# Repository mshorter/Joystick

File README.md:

# Joystick

ATMega32U4  based joystick with XBee slot

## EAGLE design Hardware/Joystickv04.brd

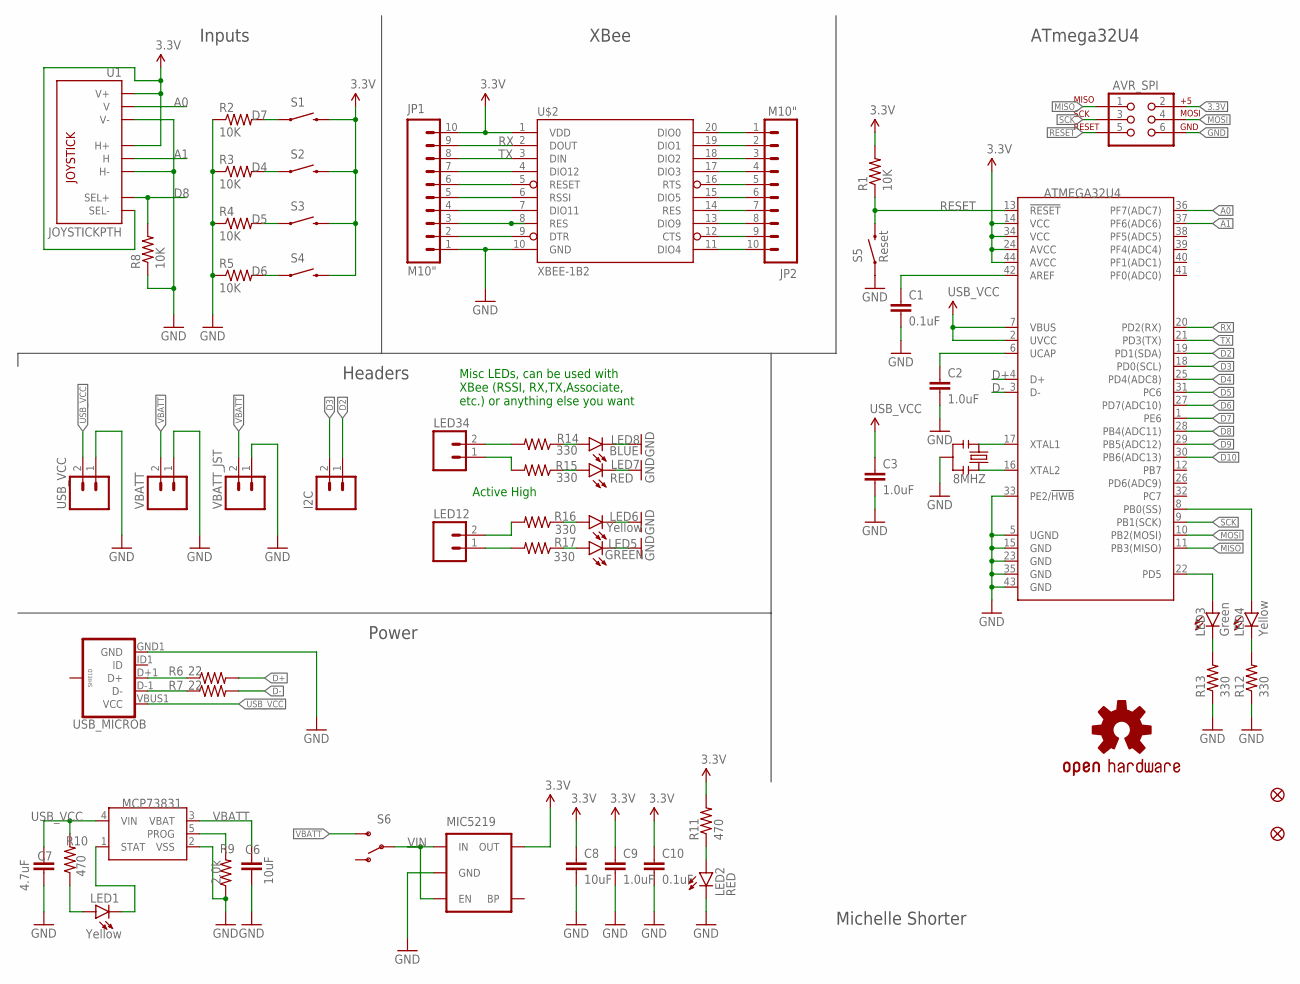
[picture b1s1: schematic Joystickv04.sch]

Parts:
ATMEGA32U4: ATMEGA32U41:1-LESS_PASTE; QFN-44-NOPAD_1:1-LESS_PASTE
AVR_SPI: AVR_SPI_PRG_6PTH; 2X3
C1, C10: 0.1uF; 0603-CAP
C2, C3, C9: 1.0uF; 0603-CAP
C6, C8: 10uF; 0603-CAP
C7: 4.7uF; 0603-CAP
FID1, FID2: FIDUCIALUFIDUCIAL; MICRO-FIDUCIAL
I2C: M02PTH; 1X02
JP1, JP2: M10"; 1X10
LED1, LED4, LED6: Yellow; LED-0603
LED2, LED7: RED; LED-0603
LED3: Green; LED-0603
LED5: GREEN; LED-0603
LED8: BLUE; LED-0603
LED12, LED34: M02PTH; 1X02
LOGO1: OSHW-LOGOM; OSHW-LOGO-M
MIC5219: V_REG_MIC5219SMD; SOT23-5
R1, R2, R3, R4, R5, R8: 10K; 0603-RES
R6, R7: 22; 0603-RES
R9: 2.0k; 0603-RES
R10, R11: 470; 0603-RES
R12, R13, R14, R15, R16, R17: 330; 0603-RES
S1, S2, S3, S4: SWITCH-MOMENTARY-212MM; TACTILE-PTH-12MM
S5: Reset; TACTILE-SWITCH-SMD
S6: SWITCH-SPDTPTH; SWITCH-SPDT
U1: JOYSTICKPTH; JOYSTICK
U4: MCP73831; SOT23-5
U$2: XBEE-1B2; XBEE-SILK
U$3: 8MHZ; RESONATOR-SMD
USB_MICROB: USB_MICROB_PLUGCONN-11752; USB-B-MICRO-SMD_V03
USB_VCC: M02PTH; 1X02
VBATT: M02PTH; 1X02
VBATT_JST: M02-JST-2MM-SMT; JST-2-SMD

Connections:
3.3V: ATMEGA32U4.14 (VCC), ATMEGA32U4.24 (AVCC), ATMEGA32U4.34 (VCC), ATMEGA32U4.44 (AVCC), AVR_SPI.2, C8.1, C9.1, C10.1, JP1.10, MIC5219.5 (OUT), R1.2, R11.2, S1.3 (2), S2.3 (2), S3.3 (2), S4.3 (2), U1.B2A (SEL-), U1.H1 (H+), U1.V1 (V+), U$2.1 (VDD)
A0: ATMEGA32U4.36 (PF7(ADC7)), U1.V2 (V)
A1: ATMEGA32U4.37 (PF6(ADC6)), U1.H2 (H)
D2: ATMEGA32U4.19 (PD1(SDA)), I2C.1
D3: ATMEGA32U4.18 (PD0(SCL)), I2C.2
D4: ATMEGA32U4.25 (PD4(ADC8)), R3.2, S2.1
D5: ATMEGA32U4.31 (PC6), R4.2, S3.1
D6: ATMEGA32U4.27 (PD7(ADC10)), R5.2, S4.1
D7: ATMEGA32U4.1 (PE6), R2.2, S1.1
D8: ATMEGA32U4.28 (PB4(ADC11)), R8.2, U1.B1A (SEL+)
D9: ATMEGA32U4.29 (PB5(ADC12))
D10: ATMEGA32U4.30 (PB6(ADC13))
D+: ATMEGA32U4.4 (D+), R6.2
D-: ATMEGA32U4.3 (D-), R7.2
GND: ATMEGA32U4.5 (UGND), ATMEGA32U4.15 (GND), ATMEGA32U4.23 (GND), ATMEGA32U4.33 (PE2/!HWB), ATMEGA32U4.35 (GND), ATMEGA32U4.43 (GND), AVR_SPI.6, C1.2, C2.2, C3.2, C6.2, C7.2, C8.2, C9.2, C10.2, JP1.1, LED2.C, LED5.C, LED6.C, LED7.C, LED8.C, MIC5219.2 (GND), R2.1, R3.1, R4.1, R5.1, R8.1, R9.1, R12.1, R13.1, S5.1, U1.H3 (H-), U1.V3 (V-), U4.2 (VSS), U$2.10 (GND), U$3.2, USB_MICROB.GND1 (GND), USB_VCC.1, VBATT.1, VBATT_JST.1
MISO: ATMEGA32U4.11 (PB3(MISO)), AVR_SPI.1
MOSI: ATMEGA32U4.10 (PB2(MOSI)), AVR_SPI.4
unnamed: ATMEGA32U4.17 (XTAL1), U$3.1
unnamed: ATMEGA32U4.42 (AREF), C1.1
unnamed: R6.1, USB_MICROB.D+1 (D+)
unnamed: JP1.2, U$2.9 (DTR)
unnamed: ATMEGA32U4.6 (UCAP), C2.1
unnamed: ATMEGA32U4.16 (XTAL2), U$3.3
unnamed: JP1.3, U$2.8 (RES)
unnamed: R7.1, USB_MICROB.D-1 (D-)
unnamed: JP1.4, U$2.7 (DIO11)
unnamed: R9.2, U4.5 (PROG)
unnamed: JP1.5, U$2.6 (RSSI)
unnamed: JP1.6, U$2.5 (RESET)
unnamed: JP1.7, U$2.4 (DIO12)
unnamed: JP2.10, U$2.11 (DIO4)
unnamed: JP2.9, U$2.12 (CTS)
unnamed: JP2.8, U$2.13 (DIO9)
unnamed: JP2.7, U$2.14 (RES)
unnamed: JP2.6, U$2.15 (DIO5)
unnamed: JP2.5, U$2.16 (RTS)
unnamed: JP2.4, U$2.17 (DIO3)
unnamed: JP2.3, U$2.18 (DIO2)
unnamed: JP2.2, U$2.19 (DIO1)
unnamed: JP2.1, U$2.20 (DIO0)
unnamed: LED2.A, R11.1
unnamed: LED1.A, R10.1
unnamed: LED1.C, U4.1 (STAT)
unnamed: ATMEGA32U4.8 (PB0(SS)), LED4.A
unnamed: LED4.C, R12.2
unnamed: LED3.C, R13.2
unnamed: ATMEGA32U4.22 (PD5), LED3.A
unnamed: LED12.1, R17.2
unnamed: LED8.A, R14.1
unnamed: LED7.A, R15.1
unnamed: LED6.A, R16.1
unnamed: LED5.A, R17.1
unnamed: LED12.2, R16.2
unnamed: LED34.1, R15.2
unnamed: LED34.2, R14.2
RESET: ATMEGA32U4.13 (!RESET), AVR_SPI.5, R1.1, S5.3 (2)
RX: ATMEGA32U4.20 (PD2(RX)), JP1.9, U$2.2 (DOUT)
SCK: ATMEGA32U4.9 (PB1(SCK)), AVR_SPI.3
TX: ATMEGA32U4.21 (PD3(TX)), JP1.8, U$2.3 (DIN)
USB_VCC: ATMEGA32U4.2 (UVCC), ATMEGA32U4.7 (VBUS), C3.1, C7.1, R10.2, U4.4 (VIN), USB_MICROB.VBUS1 (VCC), USB_VCC.2
VBATT: C6.1, S6.3 (S), U4.3 (VBAT), VBATT.2, VBATT_JST.2
VIN: MIC5219.1 (IN), MIC5219.3 (EN), S6.2

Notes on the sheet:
Misc LEDs, can be used with XBee (RSSI, RX,TX,Associate, etc.) or anything else you want
Active High
Michelle Shorter
Inputs
XBee
ATmega32U4
Headers
Power

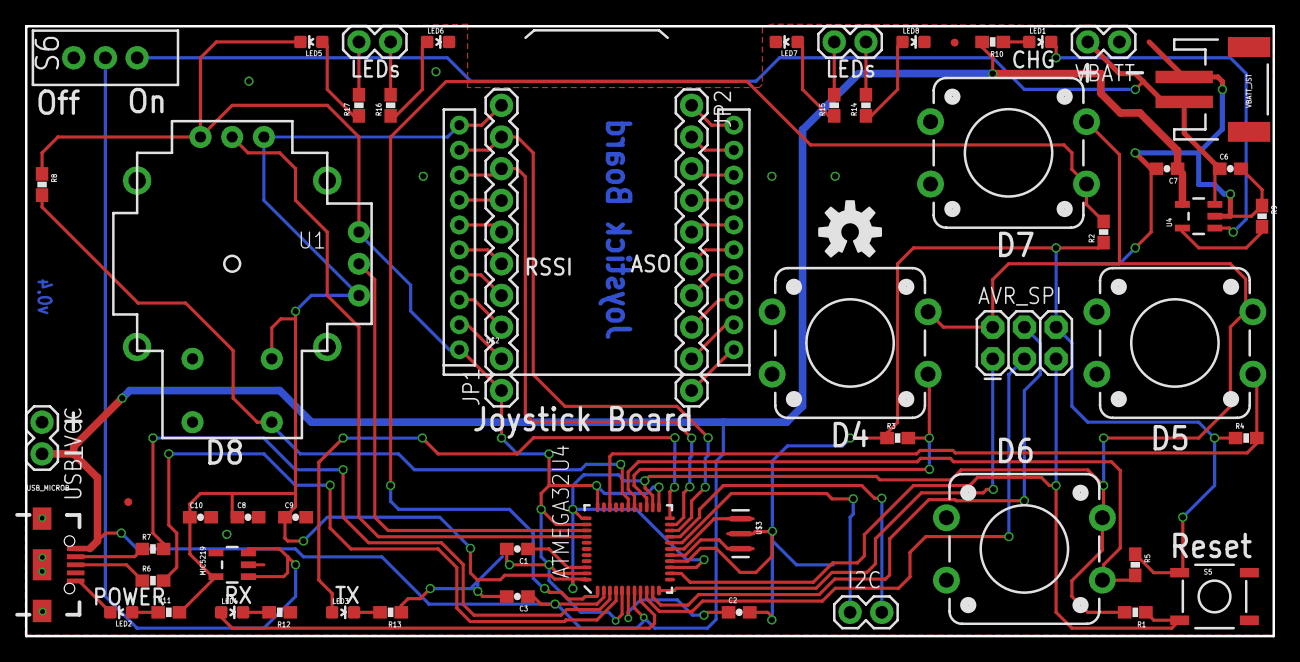
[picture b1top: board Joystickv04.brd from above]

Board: 2 copper layers, 100.0 x 48.9 mm, 58 parts (0 on the bottom side), 60 nets.

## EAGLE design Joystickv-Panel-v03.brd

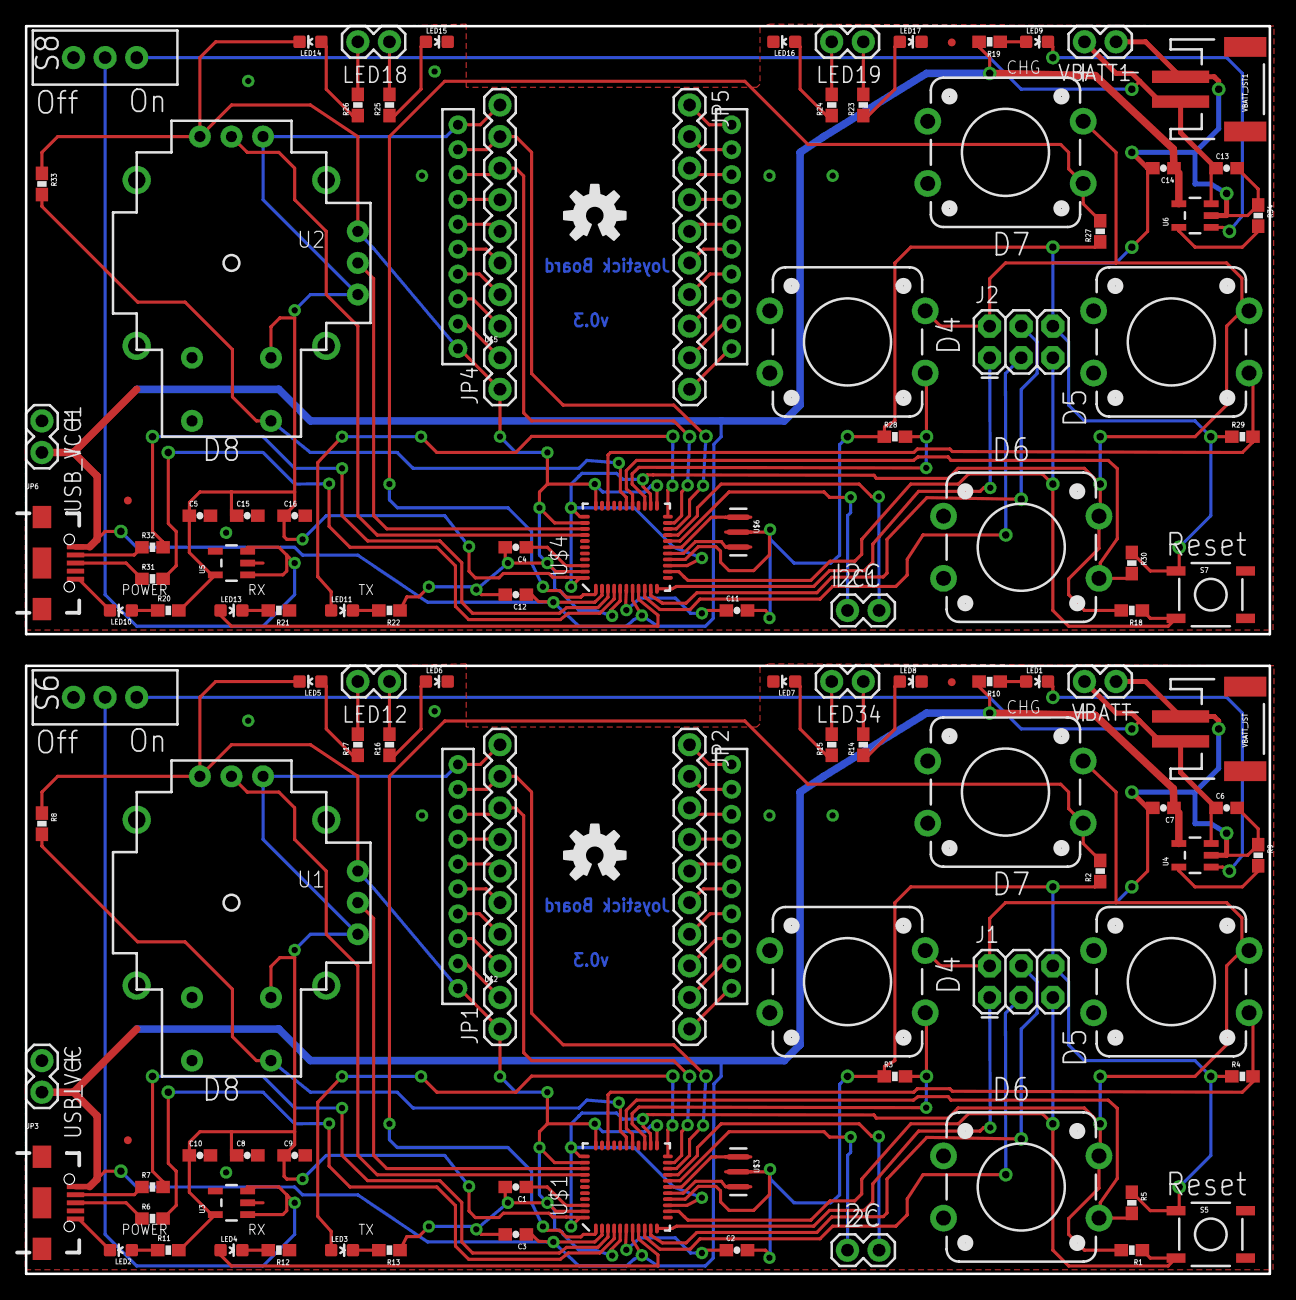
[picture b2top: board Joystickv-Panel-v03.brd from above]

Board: 2 copper layers, 100.0 x 100.3 mm, 116 parts (0 on the bottom side), 120 nets.

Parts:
C1, C4, C5, C10: 0.1uF; 0603-CAP
C2, C3, C9, C11, C12, C16: 1.0uF; 0603-CAP
C6, C8, C13, C15: 10uF; 0603-CAP
C7, C14: 4.7uF; 0603-CAP
FID1, FID2, FID3, FID4: FIDUCIALUFIDUCIAL; MICRO-FIDUCIAL
I2C, I2C1: 1X02
J1, J2: AVR_SPI_PRG_6PTH; 2X3
JP1, JP2, JP4, JP5: M10"; 1X10
JP3, JP6: USB_MICROB_PLUGCONN-11752; USB-B-MICRO-SMD_V03
LED1, LED4, LED6, LED9, LED13, LED15: Yellow; LED-0603
LED2, LED7, LED10, LED16: RED; LED-0603
LED3, LED11: Green; LED-0603
LED5, LED14: GREEN; LED-0603
LED8, LED17: BLUE; LED-0603
LED12, LED18, LED19, LED34: 1X02
LOGO1, LOGO2: OSHW-LOGOM; OSHW-LOGO-M
R1, R2, R3, R4, R5, R8, R18, R27, R28, R29, R30, R33: 10K; 0603-RES
R6, R7, R31, R32: 22; 0603-RES
R9, R34: 2.0k; 0603-RES
R10, R11, R19, R20: 470; 0603-RES
R12, R13, R14, R15, R16, R17, R21, R22, R23, R24, R25, R26: 330; 0603-RES
S1, S2, S3, S4, S9, S10, S11, S12: SWITCH-MOMENTARY-212MM; TACTILE-PTH-12MM
S5, S7: Reset; TACTILE-SWITCH-SMD
S6, S8: SWITCH-SPDT
U1, U2: JOYSTICKPTH; JOYSTICK
U3, U5: V_REG_MIC5219SMD; SOT23-5
U4, U6: MCP73831; SOT23-5
U$1, U$4: ATMEGA32U41:1-LESS_PASTE; QFN-44-NOPAD_1:1-LESS_PASTE
U$2, U$5: XBEE-1B1; XBEE-1
U$3, U$6: 8MHZ; RESONATOR-SMD
USB_VCC, USB_VCC1: 1X02
VBATT, VBATT1: 1X02
VBATT_JST, VBATT_JST1: JST-2-SMD

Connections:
3.3V: C8.1, C9.1, C10.1, J1.2, JP1.10, R1.2, R11.2, S1.3, S2.3, S3.3, S4.3, U1.B2A, U1.H1, U1.V1, U3.5, U$1.14, U$1.24, U$1.34, U$1.44, U$2.1
3.3V1: C5.1, C15.1, C16.1, J2.2, JP4.10, R18.2, R20.2, S9.3, S10.3, S11.3, S12.3, U2.B2A, U2.H1, U2.V1, U5.5, U$4.14, U$4.24, U$4.34, U$4.44, U$5.1
A0: U1.V2, U$1.36
A1: U1.H2, U$1.37
A2: U2.V2, U$4.36
A3: U2.H2, U$4.37
D1: I2C1.2, U$4.18
D2: I2C.1, U$1.19
D3: I2C.2, U$1.18
D4: R3.2, S2.1, U$1.25
D5: R4.2, S3.1, U$1.31
D6: R5.2, S4.1, U$1.27
D7: R2.2, S1.1, U$1.1
D8: R8.2, U1.B1A, U$1.28
D11: R28.2, S10.1, U$4.25
D12: R29.2, S11.1, U$4.31
D13: R30.2, S12.1, U$4.27
D14: I2C1.1, U$4.19
D15: R27.2, S9.1, U$4.1
D16: R33.2, U2.B1A, U$4.28
D+: R6.2, U$1.4
D+1: R31.2, U$4.4
D-: R7.2, U$1.3
D-1: R32.2, U$4.3
GND: C1.2, C2.2, C3.2, C6.2, C7.2, C8.2, C9.2, C10.2, J1.6, JP1.1, JP3.GND1, LED2.C, LED5.C, LED6.C, LED7.C, LED8.C, R2.1, R3.1, R4.1, R5.1, R8.1, R9.1, R12.1, R13.1, S5.1, U1.H3, U1.V3, U3.2, U4.2, U$1.5, U$1.15, U$1.23, U$1.33, U$1.35, U$1.43, U$2.10, U$3.2, USB_VCC.1, VBATT.1, VBATT_JST.1
GND1: C4.2, C5.2, C11.2, C12.2, C13.2, C14.2, C15.2, C16.2, J2.6, JP4.1, JP6.GND1, LED10.C, LED14.C, LED15.C, LED16.C, LED17.C, R21.1, R22.1, R27.1, R28.1, R29.1, R30.1, R33.1, R34.1, S7.1, U2.H3, U2.V3, U5.2, U6.2, U$4.5, U$4.15, U$4.23, U$4.33, U$4.35, U$4.43, U$5.10, U$6.2, USB_VCC1.1, VBATT1.1, VBATT_JST1.1
MISO: J1.1, U$1.11
MISO1: J2.1, U$4.11
MOSI: J1.4, U$1.10
MOSI1: J2.4, U$4.10
unnamed: U$1.17, U$3.1
unnamed: C1.1, U$1.42
unnamed: JP3.D+1, R6.1
unnamed: JP1.2, U$2.9
unnamed: C2.1, U$1.6
unnamed: U$1.16, U$3.3
unnamed: C4.1, U$4.42
unnamed: JP1.3, U$2.8
unnamed: JP3.D-1, R7.1
unnamed: JP1.4, U$2.7
unnamed: R9.2, U4.5
unnamed: JP1.5, U$2.6
unnamed: JP1.6, U$2.5
unnamed: JP1.7, U$2.4
unnamed: JP2.10, U$2.11
unnamed: JP2.9, U$2.12
unnamed: JP2.8, U$2.13
unnamed: JP2.7, U$2.14
unnamed: JP2.6, U$2.15
unnamed: JP2.5, U$2.16
unnamed: JP2.4, U$2.17
unnamed: C11.1, U$4.6
unnamed: JP2.3, U$2.18
unnamed: JP2.2, U$2.19
unnamed: JP2.1, U$2.20
unnamed: LED2.A, R11.1
unnamed: LED1.A, R10.1
unnamed: LED1.C, U4.1
unnamed: LED4.A, U$1.8
unnamed: LED4.C, R12.2
unnamed: LED3.C, R13.2
unnamed: LED3.A, U$1.22
unnamed: LED12.1, R17.2
unnamed: LED8.A, R14.1
unnamed: LED7.A, R15.1
unnamed: LED6.A, R16.1
unnamed: LED5.A, R17.1
unnamed: LED12.2, R16.2
unnamed: LED34.1, R15.2
unnamed: LED34.2, R14.2
unnamed: R34.2, U6.5
unnamed: JP4.2, U$5.9
unnamed: JP4.3, U$5.8
unnamed: JP4.4, U$5.7
unnamed: JP4.5, U$5.6
unnamed: JP4.6, U$5.5
unnamed: JP4.7, U$5.4
unnamed: JP5.10, U$5.11
unnamed: JP5.9, U$5.12
unnamed: JP5.8, U$5.13
unnamed: JP5.7, U$5.14
unnamed: JP5.6, U$5.15
unnamed: JP5.5, U$5.16
unnamed: JP5.4, U$5.17
unnamed: JP5.3, U$5.18
unnamed: JP5.2, U$5.19
unnamed: JP5.1, U$5.20
unnamed: LED9.A, R19.1
unnamed: LED9.C, U6.1
unnamed: LED10.A, R20.1
unnamed: LED13.A, U$4.8
unnamed: LED13.C, R21.2
unnamed: LED11.C, R22.2
unnamed: LED11.A, U$4.22
unnamed: LED15.A, R25.1
unnamed: LED14.A, R26.1
unnamed: LED18.1, R26.2
unnamed: LED18.2, R25.2
unnamed: LED19.1, R24.2
unnamed: LED19.2, R23.2
unnamed: LED17.A, R23.1
unnamed: LED16.A, R24.1
unnamed: JP6.D+1, R31.1
unnamed: JP6.D-1, R32.1
unnamed: U$4.17, U$6.1
unnamed: U$4.16, U$6.3
RESET: J1.5, R1.1, S5.3, U$1.13
RESET1: J2.5, R18.1, S7.3, U$4.13
RX: JP1.9, U$1.20, U$2.2
RX1: JP4.9, U$4.20, U$5.2
SCK: J1.3, U$1.9
SCK1: J2.3, U$4.9
TX: JP1.8, U$1.21, U$2.3
TX1: JP4.8, U$4.21, U$5.3
USB_VCC: C3.1, C7.1, JP3.VBUS1, R10.2, U4.4, U$1.2, U$1.7, USB_VCC.2
USB_VCC1: C12.1, C14.1, JP6.VBUS1, R19.2, U6.4, U$4.2, U$4.7, USB_VCC1.2
VBATT: C6.1, S6.3, U4.3, VBATT.2, VBATT_JST.2
VBATT1: C13.1, S8.3, U6.3, VBATT1.2, VBATT_JST1.2
VIN: S6.2, U3.1, U3.3
VIN1: S8.2, U5.1, U5.3

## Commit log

2015-03-10 Initial commit
    Almost done
2015-03-19 Review
    Review
2015-03-25 Panel
    Finished design, Panelized, and CAMed
2015-03-30 OSH Panel
    OSH requires 100mil between boards to panelize.
2015-04-28 Added Firmware
    2 Arduino sketches, one for the joystick, one for the Redbot main board.
2015-08-28 Add v0.4
    Add v0.4 which is almost storefront ready
2015-08-28 Almost ready for review
2015-09-10 Pre-review
    V05. This version has standoffs and is ready for a few comments before
    bringing to engineering review

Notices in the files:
parts and their libraries:
SparkFun-Capacitors: Licensing: CC v3.0 Share-Alike You are welcome to use this library for commercial purposes.
SparkFun-Resistors: Licensing: Creative Commons ShareAlike 4.0 International - https://creativecommons.org/licenses/by-sa/4.0
SparkFun-Aesthetics: Released under the Creative Commons
